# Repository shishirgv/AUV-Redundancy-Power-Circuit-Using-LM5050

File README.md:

LM5050 Dual Input Redundancy Circuit:-

Provide seamless power redundancy between
main battery and backup battery.

Each battery feeds the output through an
LM5050-controlled MOSFET acting as an ideal diode.

MOSFET Selection:-

Part: SUM40N10-30

Reasons:-
- Low RDS(on)
- Suitable VGS(th)[The selected MOSFET has a low gate threshold voltage (typically 1–4 V), allowing reliable enhancement by the LM5050 gate drive circuitry while maintaining a low RDS(on)]
- High current capability
- Used in TI reference design

PCB Design Points:-
- 1 mm power traces
- Ground pour on bottom layer
- ERC and DRC clean

Improvements:- 
- A zener diode can be added for more safety
- The routing should follow the 90 degree rule
- Pin mapping of used mosfet should be verified before confirming schematic

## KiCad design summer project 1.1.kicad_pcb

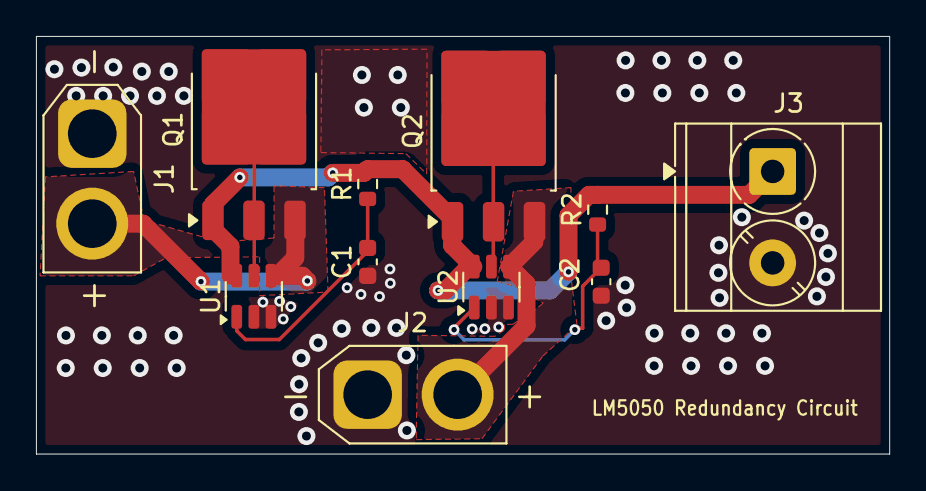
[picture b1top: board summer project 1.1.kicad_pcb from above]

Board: 2 copper layers, 47.4 x 23.2 mm, 11 parts (0 on the bottom side), 8 nets.

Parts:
C1, C2: 0.1u; C_0603_1608Metric
J1, J2: Conn_01x02_Socket; AMASS_XT30U-F_1x02_P5.0mm_Vertical
J3: Screw_Terminal_01x02; TerminalBlock_Phoenix_MKDS-3-2-5.08_1x02_P5.08mm_Horizontal
Q1, Q2: NMOS; TO-252-3_TabPin2
R1, R2: 100; R_0603_1608Metric
U1, U2: LM5050-1_mod2; TSOT-23-6

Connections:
BACKUP BATT: J2.2, Q2.3 (S), U2.4 (IN)
GND: C1.1, C2.1, J1.1, J2.1, J3.2, U1.2 (GND), U1.3 (OFF), U2.2 (GND), U2.3 (OFF)
MAIN BATT: J1.2, Q1.3 (S), U1.4 (IN)
unnamed: Q1.2 (G), U1.5 (GATE)
unnamed: Q2.2 (G), U2.5 (GATE)
unnamed: C1.2, R1.1, U1.1 (VS)
unnamed: C2.2, R2.1, U2.1 (VS)
VCC (Vout): J3.1, Q1.1 (D), Q2.1 (D), R1.2, R2.2, U1.6 (OUT), U2.6 (OUT)

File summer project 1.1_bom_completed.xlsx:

Id | Designator | Footprint | Quantity | Designation | Part Number
1 | J3 | TerminalBlock_Phoenix_MKDS-3-2-5.08_1x02_P5.08mm_Horizontal | 1 | Screw_Terminal_01x02 | 1711725(Phoenix Contact)
2 | U1,U2 | TSOT-23-6 | 2 | LM5050-1_mod2 | LM5050-1-Q1
3 | Q1,Q2 | TO-252-3_TabPin2 | 2 | NMOS | SUM40N10-30
4 | J2,J1 | AMASS_XT30U-F_1x02_P5.0mm_Vertical | 2 | Conn_01x02_Socket | XT30UPB-F
5 | R1,R2 | R_0603_1608Metric | 2 | 100 | 311-100HRCT-ND(Digikey)
6 | C1,C2 | C_0603_1608Metric | 2 | 0.1u | 490-1315-1-ND(Digikey)

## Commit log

2026-06-02 LM5050 Symbol Edited
2026-06-02 Schematic Design Completed
2026-06-02 Placement Of Components Completed
2026-06-02 Routing Completed
2026-06-02 bill of materials completed
2026-06-02 Pages Titled
2026-06-02 Moved multiple files into a folder
2026-06-03 final
2026-06-03 symbol design
2026-06-03 files moved
2026-06-06 final commit
2026-06-06 extras
